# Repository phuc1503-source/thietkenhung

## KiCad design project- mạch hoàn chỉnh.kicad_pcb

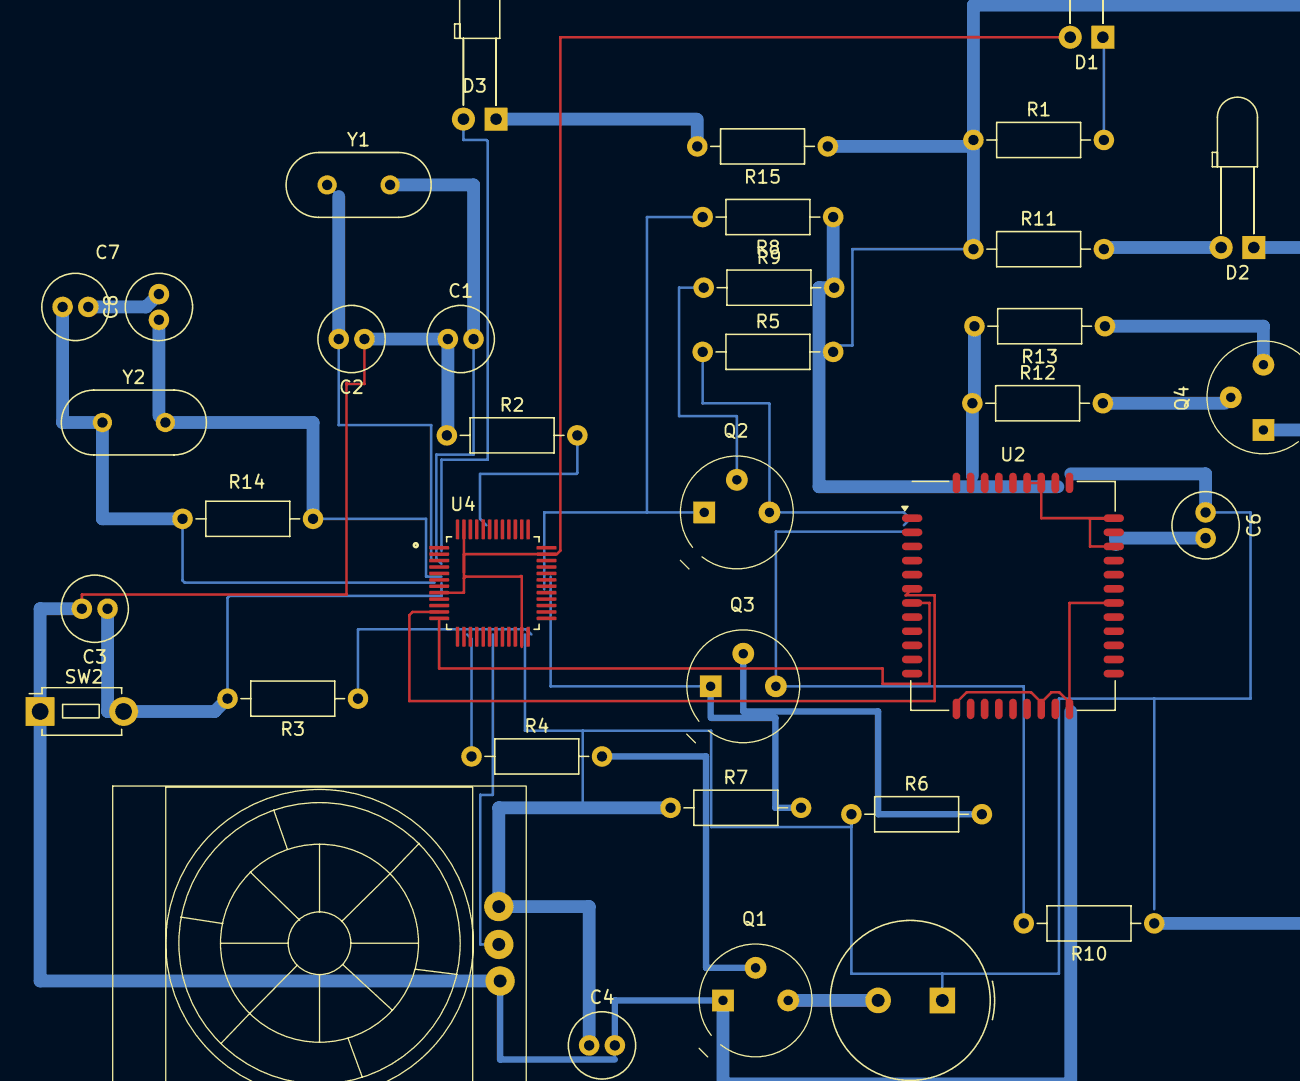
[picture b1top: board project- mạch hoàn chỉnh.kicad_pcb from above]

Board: 2 copper layers, 36 parts (0 on the bottom side), 31 nets.

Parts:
BZ1: Buzzer; Buzzer_TDK_PS1240P02BT_D12.2mm_H6.5mm
C1, C2, C3, C4, C6: C; C_Radial_D5.0mm_H11.0mm_P2.00mm
C7: C7; C_Radial_D5.0mm_H11.0mm_P2.00mm
C8: C8; C_Radial_D5.0mm_H11.0mm_P2.00mm
D1: LED_Filled; LED_D3.0mm_Horizontal_O6.35mm_Z10.0mm
D2, D3: LED; LED_D3.0mm_Horizontal_O6.35mm_Z10.0mm
Q1: 2N2219A; TO-39-3
Q2, Q3, Q4: NPN; TO-39-3
R1, R15: 510; R_Axial_DIN0207_L6.3mm_D2.5mm_P10.16mm_Horizontal
R2: 100k; R_Axial_DIN0207_L6.3mm_D2.5mm_P10.16mm_Horizontal
R3, R4: R; R_Axial_DIN0207_L6.3mm_D2.5mm_P10.16mm_Horizontal
R5, R6: 47k; R_Axial_DIN0207_L6.3mm_D2.5mm_P10.16mm_Horizontal
R7, R8, R9, R10: 4.7k; R_Axial_DIN0207_L6.3mm_D2.5mm_P10.16mm_Horizontal
R11, R12: 1k; R_Axial_DIN0207_L6.3mm_D2.5mm_P10.16mm_Horizontal
R13: 10k; R_Axial_DIN0207_L6.3mm_D2.5mm_P10.16mm_Horizontal
R14: 1M; R_Axial_DIN0207_L6.3mm_D2.5mm_P10.16mm_Horizontal
SW2: SW_Push; SW_PUSH_1P1T_6x3.5mm_H5.0_APEM_MJTP1250
U1: hc-sr501
U2: SIMA7680; SIMCom_SIM800C
U4: STM32F103C8T6; QFP50P900X900X160-48N
Y1: Crystal; Crystal_HC18-U_Vertical
Y2: 32k; Crystal_HC18-U_Vertical

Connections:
+3.3V: R1.1, R5.2, R10.1, R11.1, R15.1
Earth: C1.1, C2.1, C3.2, C4.2, C6.2, Q1.1 (E), R2.1, SW2.1, U1.3, U2.8 (GND), U2.13 (GND), U2.19 (GND), U2.21 (GND), U2.27 (GND), U2.30 (GND), U2.31 (GND), U2.33 (GND), U2.36 (GND), U2.37 (GND)
GND: D1.2 (A), U4.8 (VSSA), U4.23 (VSS), U4.35 (VSS), U4.47 (VSS)
GNDREF: Q4.3 (E), R13.1
unnamed: BZ1.2 (-), Q1.3 (C)
unnamed: C7.2, C8.2
unnamed: D1.1 (K), R1.2
unnamed: D2.2 (A), R11.2
unnamed: D2.1 (K), Q4.1 (C)
unnamed: D3.2 (A), U4.2 (PC13-TAMPER-RTC)
unnamed: D3.1 (K), R15.2
unnamed: Q1.2 (B), R4.2
unnamed: Q2.2 (B), R9.1
unnamed: Q2.1 (C), R8.2, U4.30 (PA9)
unnamed: Q2.3 (E), R5.1, U2.1 (UART1_TXD)
unnamed: Q3.2 (B), R6.2
unnamed: Q3.1 (C), R7.2, U4.31 (PA10)
unnamed: Q3.3 (E), R10.2, U2.2 (UART1_RXD)
unnamed: Q4.2 (B), R12.2
unnamed: R12.1, R13.2, U2.41 (NETLIGHT)
unnamed: U2.6 (UART1_DTR), U4.11 (PA1)
unnamed: U2.7 (UART1_RI), U4.12 (PA2)
unnamed: R2.2, U4.44 (BOOT0)
unnamed: C3.1, R3.2, SW2.2, U4.7 (NRST)
unnamed: R4.1, U4.15 (PA5)
unnamed: U1.2, U4.19 (PB1)
unnamed: C1.2, U4.3 (PC14-OSC32_IN), Y1.2
unnamed: C2.2, U4.4 (PC15-OSC32_OUT), Y1.1
unnamed: C8.1, R14.2, U4.5 (PD0_OSC_IN), Y2.2
unnamed: C7.1, R14.1, U4.6 (PD1_OSC_OUT), Y2.1
VCC: BZ1.1 (+), C4.1, C6.1, R3.1, R6.1, R7.1, R8.1, R9.2, U1.1, U2.34 (VBAT), U2.35 (VBAT), U4.24 (VDD), U4.36 (VDD), U4.48 (VDD)
